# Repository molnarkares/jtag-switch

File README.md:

# JTAG Switch

A hardware and software solution for automatically switching JTAG debuggers between multiple test benches in automated hardware testing environments.

## Overview

The JTAG Switch enables efficient sharing of expensive or limited-availability JTAG debuggers across multiple hardware test benches. Instead of purchasing dedicated debuggers for each test bench in CI/CD pipelines, a single JTAG debugger can be dynamically routed between two independent test targets, maximizing hardware utilization while maintaining testing throughput.

## Project Structure

This repository contains both hardware and software components:

### Hardware (`hw/`)

Arduino shield PCB design for JTAG multiplexing hardware:
- **KiCad Project**: Complete schematic and PCB layout
- **Files**: `jtag_switch.kicad_sch`, `jtag_switch.kicad_pcb`
- **Interface**: Arduino-compatible headers for connection to microcontroller EVBs
- **Switching**: Two independent GPIO-controlled select lines for JTAG routing

The shield plugs into any Arduino-compatible microcontroller evaluation board and provides the physical JTAG switching circuitry.

### Software (`sw/`)

Zephyr RTOS firmware for controlling the JTAG switch hardware:
- **Platform**: Runs on any Zephyr-supported microcontroller with Arduino headers
- **Supported Boards**:
  - FRDM-K64F (NXP Kinetis K64) - primary development board with Ethernet
  - FRDM-MCXC444 (NXP MCX C444) - development board with USB serial only
- **Control Interfaces**:
  - USB serial shell (115200 baud)
  - Ethernet REST API with JSON endpoints
  - Web-based UI with real-time control
- **Safety**: Enforces mutual exclusion - both GPIO select lines never HIGH simultaneously

See [sw/jtag-switch/README.md](sw/jtag-switch/README.md) for complete software documentation including build instructions, API reference, and testing information.

## Quick Start

### Hardware Setup

1. Open the KiCad project in `hw/` to view or manufacture the Arduino shield
2. Assemble the shield and mount it on a compatible microcontroller EVB
3. Connect JTAG debugger and target devices to the shield connectors

### Software Setup

```bash
# Navigate to software directory
cd sw

# Set up Zephyr environment
source .venv/bin/activate
source zephyr/zephyr-env.sh

# Build and flash firmware (FRDM-K64F)
west build -b frdm_k64f jtag-switch
west flash

# Or build and flash firmwarefor FRDM MCXC444
west build -b frdm_mcxc444 jtag-switch
west flash

### Usage

**Via USB Serial:**
```bash
screen /dev/ttyACM0 115200
uart:~$ jtag status
uart:~$ jtag select0 1
```

**Via REST API:**
```bash
# Get current status
curl http://192.168.1.100/api/status

# Switch to connector 1 on select line 0
curl -X POST "http://192.168.1.100/api/select?line=0&connector=1"
```

**Via Web UI:**

Navigate to `http://192.168.1.100/` in a web browser for graphical control.

## Documentation

- **Software Details**: [sw/jtag-switch/README.md](sw/jtag-switch/README.md)
- **Software Development Guide**: [sw/jtag-switch/CLAUDE.md](sw/jtag-switch/CLAUDE.md)
- **Hardware Design**: Open `hw/jtag_switch.kicad_pro` in KiCad

## License

SPDX-License-Identifier: Apache-2.0

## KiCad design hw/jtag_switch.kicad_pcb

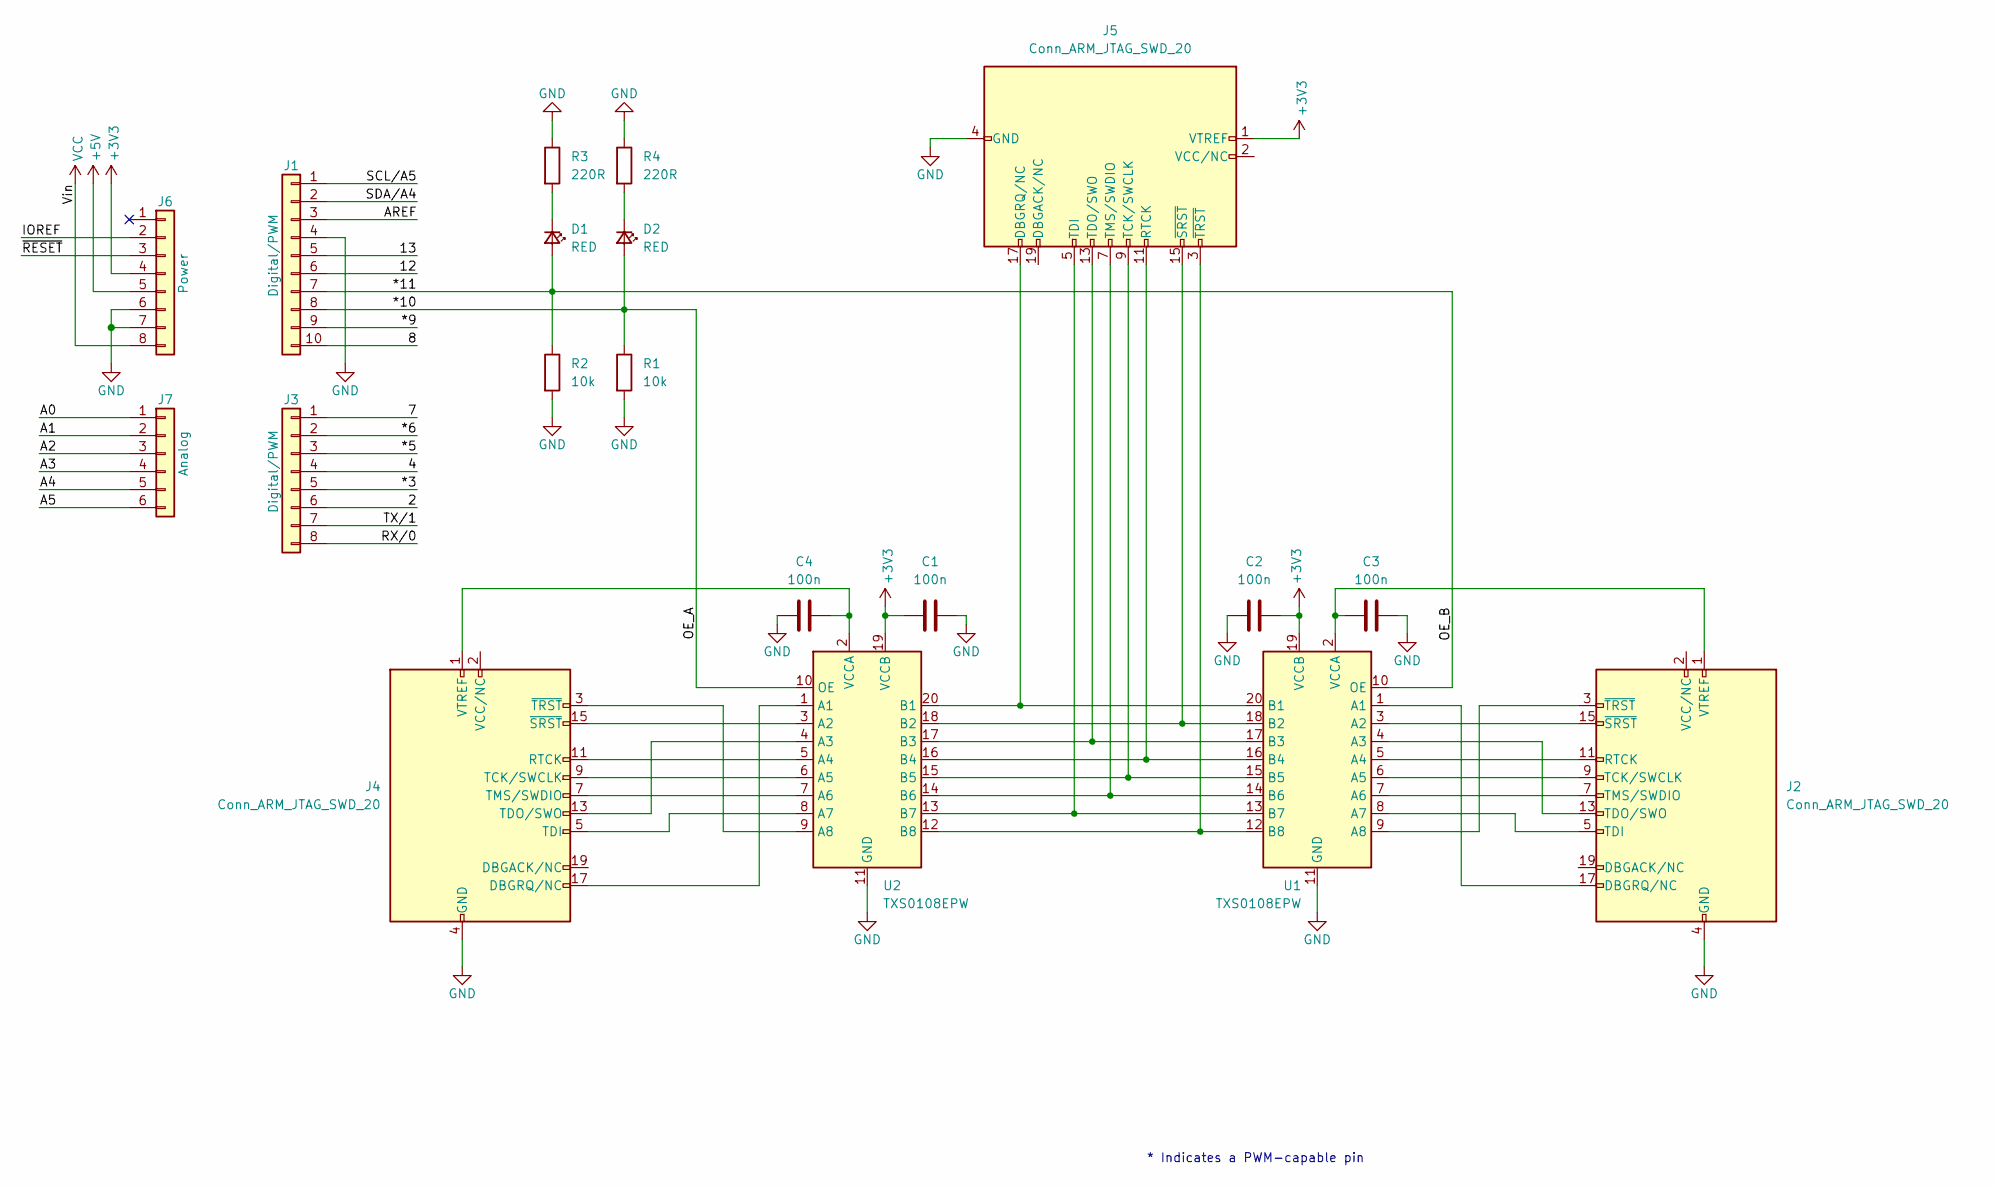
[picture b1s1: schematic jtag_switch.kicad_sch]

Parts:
C1, C2, C3, C4: 100n; C_0603_1608Metric_Pad1.08x0.95mm_HandSolder
D1, D2: RED; LED_0805_2012Metric
J1: Digital/PWM; PinSocket_1x10_P2.54mm_Vertical
J2, J4: Conn_ARM_JTAG_SWD_20; IDC-Header_2x10_P2.54mm_Vertical
J3: Digital/PWM; PinSocket_1x08_P2.54mm_Vertical
J5: Conn_ARM_JTAG_SWD_20; IDC-Header_2x10_P2.54mm_Horizontal
J6: Power; PinSocket_1x08_P2.54mm_Vertical
J7: Analog; PinSocket_1x06_P2.54mm_Vertical
R1, R2: 10k; R_0603_1608Metric_Pad0.98x0.95mm_HandSolder
R3, R4: 220R; R_0603_1608Metric_Pad0.98x0.95mm_HandSolder
U1, U2: TXS0108EPW; TSSOP-20_4.4x6.5mm_P0.65mm

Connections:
+3V3: C1.1, C2.2, J5.1 (VTREF), J6.4, U1.19 (VCCB), U2.19 (VCCB)
+5V: J6.5
/2: J3.6
/4: J3.4
/7: J3.1
/8: J1.10
/12: J1.6
/13: J1.5
/*3: J3.5
/*5: J3.3
/*6: J3.2
/*9: J1.9
/*10: D2.2 (A), J1.8, R1.1, U2.10 (OE)
/*11: D1.2 (A), J1.7, R2.1, U1.10 (OE)
/A0: J7.1
/A1: J7.2
/A2: J7.3
/A3: J7.4
/A4: J7.5
/A5: J7.6
/AREF: J1.3
/IOREF: J6.2
/RX/0: J3.8
/SCL/A5: J1.1
/SDA/A4: J1.2
/TX/1: J3.7
/~RESET: J6.3
GND: C1.2, C2.1, C3.2, C4.1, J1.4, J2.4 (GND), J2.6 (GND), J2.8 (GND), J2.10 (GND), J2.12 (GND), J2.14 (GND), J2.16 (GND), J2.18 (GND), J2.20 (GND), J4.4 (GND), J4.6 (GND), J4.8 (GND), J4.10 (GND), J4.12 (GND), J4.14 (GND), J4.16 (GND), J4.18 (GND), J4.20 (GND), J5.4 (GND), J5.6 (GND), J5.8 (GND), J5.10 (GND), J5.12 (GND), J5.14 (GND), J5.16 (GND), J5.18 (GND), J5.20 (GND), J6.6, J6.7, R1.2, R2.2, R3.1, R4.1, U1.11 (GND), U2.11 (GND)
unnamed: D1.1 (K), R3.2
unnamed: D2.1 (K), R4.2
unnamed: J2.17 (DBGRQ/NC), U1.1 (A1)
unnamed: J2.11 (RTCK), U1.5 (A4)
unnamed: J2.9 (TCK/SWCLK), U1.6 (A5)
unnamed: J2.5 (TDI), U1.8 (A7)
unnamed: J2.13 (TDO/SWO), U1.4 (A3)
unnamed: J2.7 (TMS/SWDIO), U1.7 (A6)
unnamed: C3.1, J2.1 (VTREF), U1.2 (VCCA)
unnamed: J2.15 (~SRST), U1.3 (A2)
unnamed: J2.3 (~TRST), U1.9 (A8)
unnamed: J4.17 (DBGRQ/NC), U2.1 (A1)
unnamed: J4.11 (RTCK), U2.5 (A4)
unnamed: J4.9 (TCK/SWCLK), U2.6 (A5)
unnamed: J4.5 (TDI), U2.8 (A7)
unnamed: J4.13 (TDO/SWO), U2.4 (A3)
unnamed: J4.7 (TMS/SWDIO), U2.7 (A6)
unnamed: C4.2, J4.1 (VTREF), U2.2 (VCCA)
unnamed: J4.15 (~SRST), U2.3 (A2)
unnamed: J4.3 (~TRST), U2.9 (A8)
unnamed: J5.17 (DBGRQ/NC), U1.20 (B1), U2.20 (B1)
unnamed: J5.11 (RTCK), U1.16 (B4), U2.16 (B4)
unnamed: J5.9 (TCK/SWCLK), U1.15 (B5), U2.15 (B5)
unnamed: J5.5 (TDI), U1.13 (B7), U2.13 (B7)
unnamed: J5.13 (TDO/SWO), U1.17 (B3), U2.17 (B3)
unnamed: J5.7 (TMS/SWDIO), U1.14 (B6), U2.14 (B6)
unnamed: J5.15 (~SRST), U1.18 (B2), U2.18 (B2)
unnamed: J5.3 (~TRST), U1.12 (B8), U2.12 (B8)
VCC: J6.8

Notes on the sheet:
* Indicates a PWM-capable pin

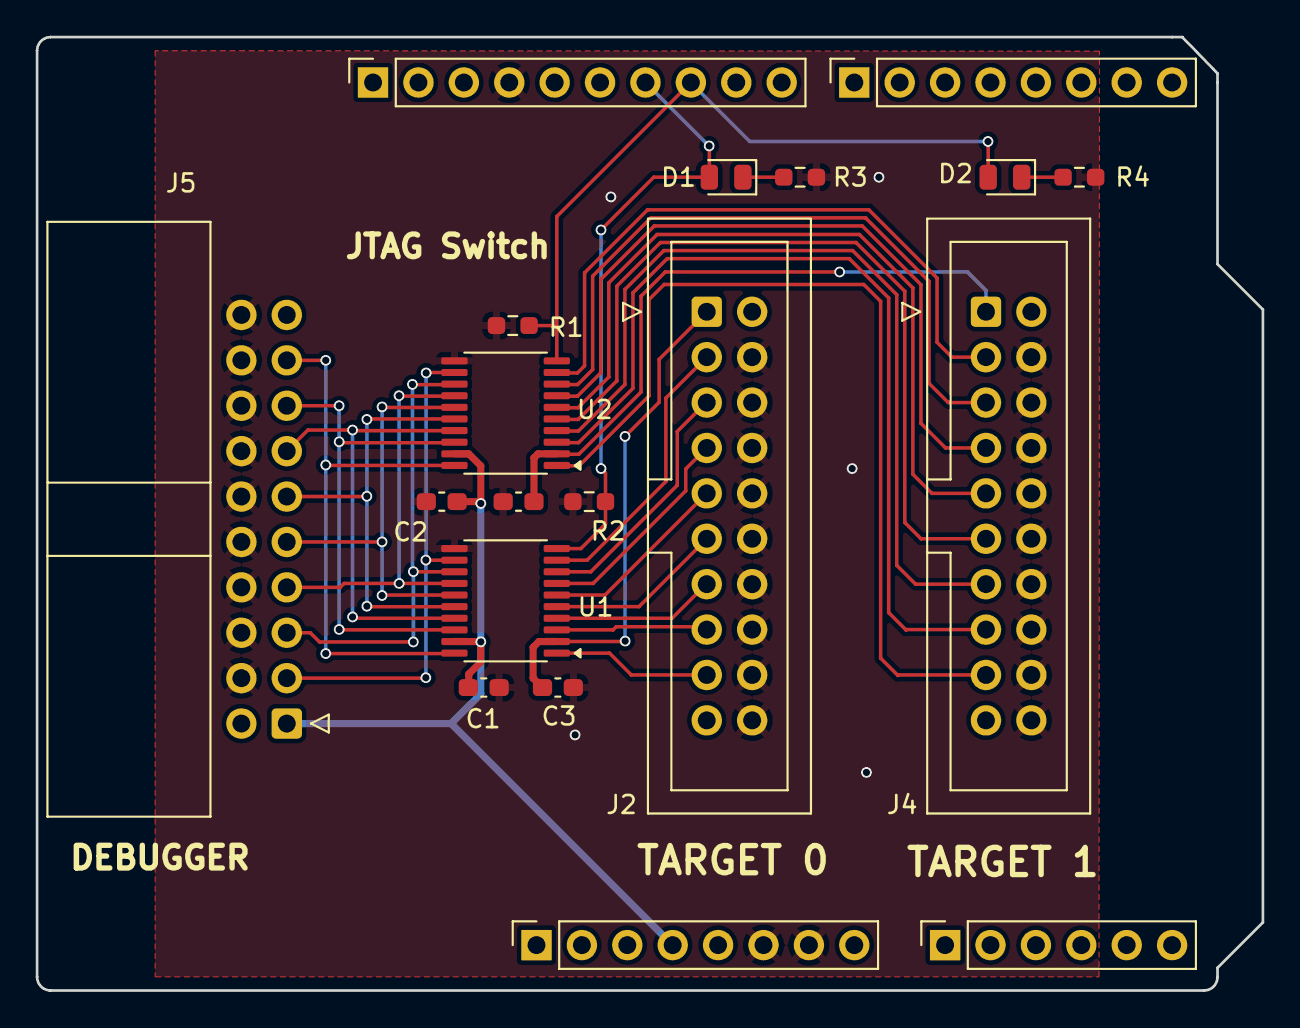
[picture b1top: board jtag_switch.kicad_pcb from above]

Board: 2 copper layers, 68.6 x 53.3 mm, 19 parts (0 on the bottom side), 32 nets.

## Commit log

2025-12-04 iBoard design files added
2025-12-05 iinital commit for jtag-switch
2025-12-05 sw files relocatedwq
2025-12-05 updated readme with main use case
2025-12-05 added gitignore
2025-12-05 iadded readme
2025-12-05 ignored local doc folder with PDFs
2025-12-05 Using gziped web resources to save flash
2025-12-05 reduced RAM consumption
2025-12-05 Synching sw gpio pins to HW
2025-12-05 Fix README typos
2025-12-06 added design rules
2025-12-06 HW v1.0 sent to Aisler
2025-12-06 added test support for multiple boards
2025-12-06 added support for FRDM MCX C444
2025-12-07 removed rules (vendor specific)
2025-12-07 removed local references from README.md
2025-12-07 Added step-by-step instructions for fresh install
2025-12-07 Add Solderpad Hardware License v2.1 to HW
2025-12-07 Fix copyright formatting in LICENSE file
2025-12-07 removed Nucleo board until VID and PID is defined
2025-12-07 added simulated FRDMK64F node
2025-12-07 added Kicad CICD automation
2025-12-07 fixing build errors in kicad-ci.yaml
2025-12-07 Fixed kibot yam
2025-12-07 Fixing kibot version in control file
2025-12-07 changed kibot version for compatibility
2025-12-07 updated kicad ci workflow WIP
2025-12-07 adding python install to kicad docker for cicd
2025-12-07 triggering kibot
2025-12-07 switching to full kicad docker mage
2025-12-07 Using appimage because kicad docker has limitations with python
2025-12-07 using custom image for generating hw files
2025-12-07 revisited approach to generate kicad gerbers and documentation
2025-12-07 idefinition of artifact storage for HW
2025-12-07 Updated path of fabrication files
2025-12-07 updated release control
2025-12-07 updated todo in kibot control file
2025-12-07 added basic west build
2025-12-07 renamed build control
2025-12-07 added test explanation for simulated node
2025-12-07 cicd build fix
2025-12-07 fixing build scrip
2025-12-07 fixing ci script for west build
2025-12-07 fixing sw build
2025-12-07 fixing west build on cicd
2025-12-07 fixinb west build on cicd
2025-12-07 added base-path to zephyr init
2025-12-07 fixing build step
2025-12-07 adjusting cicd build step
2025-12-07 temporary fix on west build
2025-12-07 fixing west build
2025-12-07 corrected west build in cicd
2025-12-08 Fixed frankenconfig of virtual target for Ethernet tests
2025-12-09 Adding renode based tests for github actions
2025-12-09 fixing build for renode simulated target
2025-12-09 improving cicd build time
2025-12-20 Added USB PID and VID
